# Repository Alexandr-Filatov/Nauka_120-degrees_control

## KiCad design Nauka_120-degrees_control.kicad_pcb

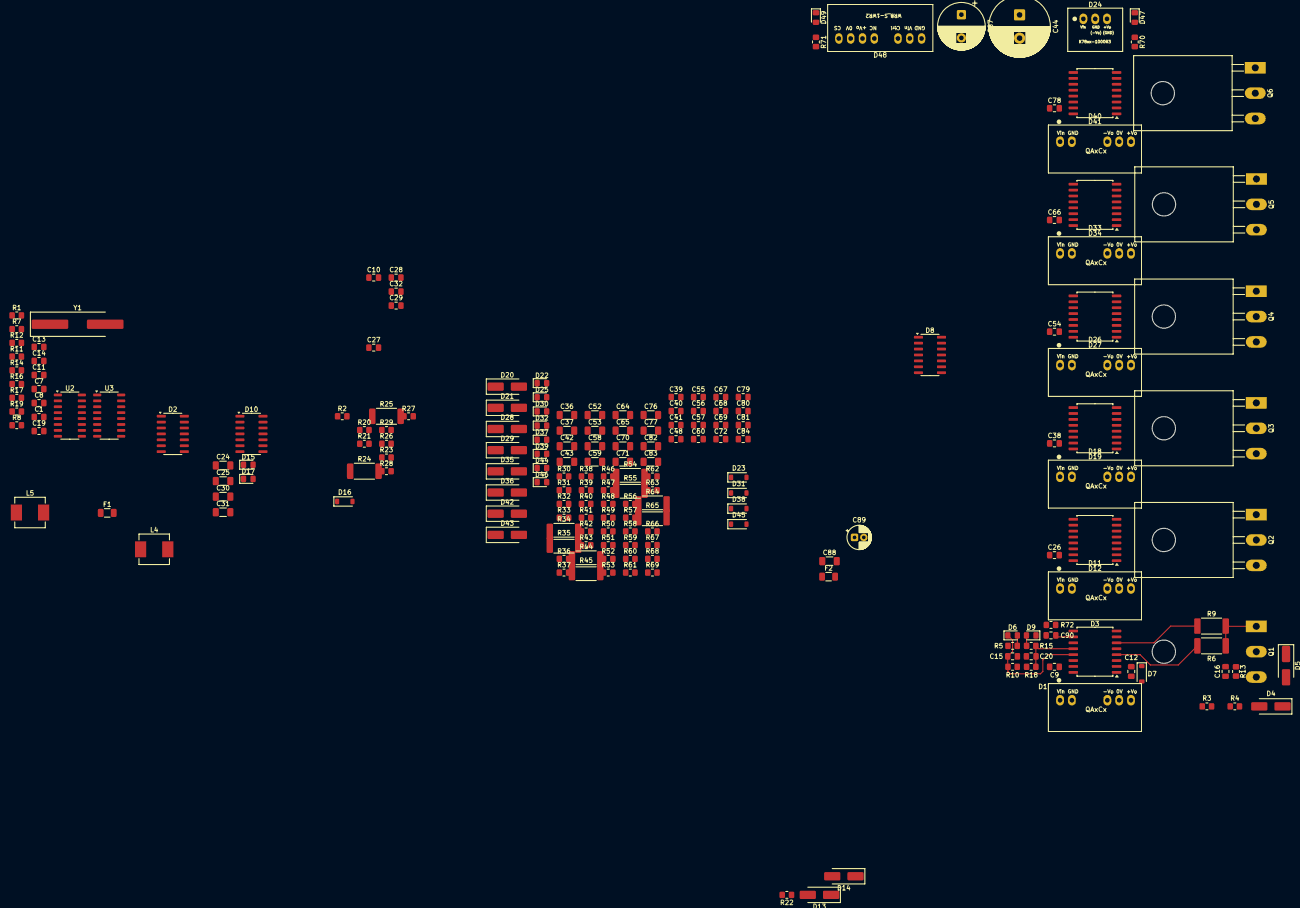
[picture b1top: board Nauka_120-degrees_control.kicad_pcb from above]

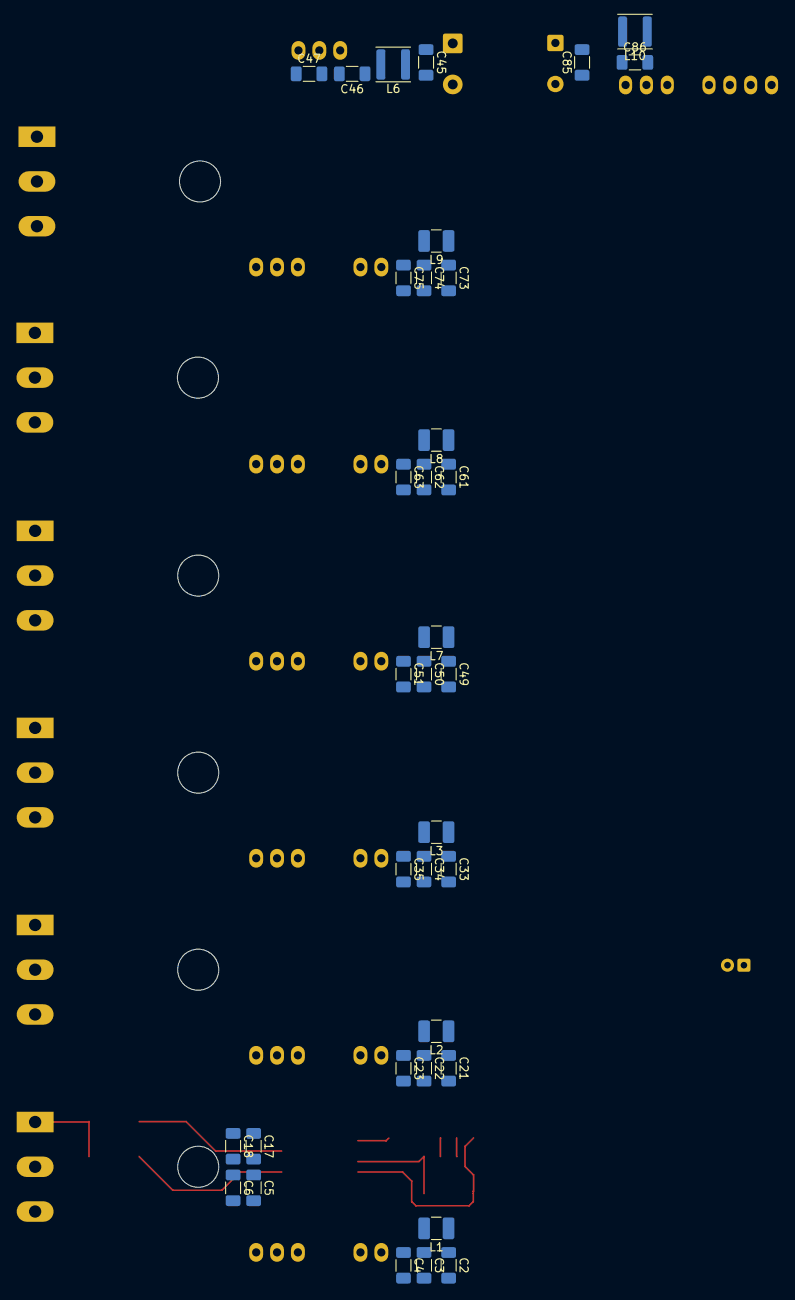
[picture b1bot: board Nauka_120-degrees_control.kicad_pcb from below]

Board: 4 copper layers, 232 parts (35 on the bottom side), 130 nets.

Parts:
C1, C7, C8, C10, C11, C19: 100n; C_0805_2012Metric_Pad1.18x1.45mm_HandSolder
C2, C3, C21, C22, C33, C34, C45, C49, C50, C61, C62, C73, C74, C85: 4.7u; C_1206_3216Metric_Pad1.33x1.80mm_HandSolder
C4, C23, C35, C51, C63, C75: 100p; C_1206_3216Metric_Pad1.33x1.80mm_HandSolder
C5, C6, C17, C18, C24, C25, C30, C31, C36, C37, C42, C43, C46, C52, C53, C58, C59, C64, C65, C70, C71, C76, C77, C82, C83, C86, C88: 10u; C_1206_3216Metric_Pad1.33x1.80mm_HandSolder
C9, C26, C38, C54, C66, C78: 2.2u; C_0805_2012Metric_Pad1.18x1.45mm_HandSolder
C12, C27, C39, C55, C67, C79: 100p; C_0805_2012Metric_Pad1.18x1.45mm_HandSolder
C13, C14: 20p; C_0805_2012Metric_Pad1.18x1.45mm_HandSolder
C15, C20, C29, C32, C40, C48, C57, C60, C68, C72, C81, C84, C90: 56p; C_0805_2012Metric_Pad1.18x1.45mm_HandSolder
C16, C28, C41, C56, C69, C80: 10n; C_0805_2012Metric_Pad1.18x1.45mm_HandSolder
C44: 680u; CP_Radial_D13.0mm_P5.00mm
C47: 22u; C_1206_3216Metric_Pad1.33x1.80mm_HandSolder
C87: 330u; CP_Radial_D10.0mm_P5.00mm
C89: 100u; CP_Radial_D5.0mm_P2.00mm
D1, D11, D18, D26, D33, D40: QA151C3; QAxCx
D2, D10: SOIC-14_3.9x8.7mm_P1.27mm
D3, D12, D19, D27, D34, D41: NSI6651; SOIC-16W_7.5x10.3mm_P1.27mm
D4, D5, D13, D14, D20, D21, D28, D29, D35, D36, D42, D43: D_Small; D_SMA_Handsoldering
D6, D9, D15, D17, D22, D25, D30, D32, D37, D39, D44, D46, D47, D49: LED_0805_2012Metric_Pad1.15x1.40mm_HandSolder
D7, D16, D23, D31, D38, D45: D_SOD-123
D8: SO-14_3.9x8.65mm_P1.27mm
D24: K7815-1000R3; K78xx-1000R3
D48: WRB2405S-1WR2; WRB_S-1WR2
F1, F2: 0466002.NR; Fuse_1206_3216Metric
L1, L2, L3, L7, L8, L9: 22u; L_1210_3225Metric_Pad1.42x2.65mm_HandSolder
L4, L5: 47u; L_Vishay_IHLP-2525
L6: 12u; L_APV_ANR4030
L10: 4.7u; L_APV_ANR4030
Q1, Q2, Q3, Q4, Q5, Q6: C2M0280120D; TO-247-3_Horizontal_TabUp
R1: 10M; R_0805_2012Metric_Pad1.20x1.40mm_HandSolder
R2, R20, R30, R40, R50, R60: 510; R_0805_2012Metric_Pad1.20x1.40mm_HandSolder
R3, R5, R18, R21, R23, R29, R31, R33, R39, R41, R43, R49, R51, R53, R59, R61, R63, R69, R71: 1k; R_0805_2012Metric_Pad1.20x1.40mm_HandSolder
R4, R22, R32, R42, R52, R62: Rdesat; R_0805_2012Metric_Pad1.20x1.40mm_HandSolder
R6, R9, R24, R25, R34, R35, R44, R45, R54, R55, R64, R65: 3; R_2512_6332Metric_Pad1.40x3.35mm_HandSolder
R7: 100k; R_0805_2012Metric_Pad1.20x1.40mm_HandSolder
R8, R11, R12, R14, R16, R17, R19: 0; R_0805_2012Metric_Pad1.20x1.40mm_HandSolder
R10, R13, R26, R27, R36, R37, R46, R47, R56, R57, R66, R67: 10k; R_0805_2012Metric_Pad1.20x1.40mm_HandSolder
R15, R28, R38, R48, R58, R68: 560; R_0805_2012Metric_Pad1.20x1.40mm_HandSolder
R70: 3k; R_0805_2012Metric_Pad1.20x1.40mm_HandSolder
R72: 120; R_0805_2012Metric_Pad1.20x1.40mm_HandSolder
U2: 4040; SO-16_3.9x9.9mm_P1.27mm
U3: 4017; SO-16_3.9x9.9mm_P1.27mm
Y1: 4.9152M; Crystal_SMD_HC49-SD_HandSoldering

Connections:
+5V: C1.2, C7.2, C8.2, C9.2, C10.2, C11.2, C19.2, C26.2, C38.2, C54.2, C66.2, C78.2, C89.1, D2.14 (VCC), D3.15 (Vcc1), D8.14 (VCC), D10.14 (VCC), D12.15 (Vcc1), D19.15 (Vcc1), D27.15 (Vcc1), D34.15 (Vcc1), D41.15 (Vcc1), D48.6 (+Vo), R5.2, R10.2, R18.2, R23.2, R26.2, R29.2, R33.2, R36.2, R39.2, R43.2, R46.2, R49.2, R53.2, R56.2, R59.2, R63.2, R66.2, R69.2, R71.2, U2.16 (VDD), U3.16 (VDD)
+15V: C2.1, C21.1, C33.1, C47.1, C49.1, C61.1, C73.1, D24.3 (+Vo(GND)), L1.1, L2.1, L3.1, L7.1, L8.1, L9.1, R70.2
+15V_H1: C5.2, C6.2, D1.7 (+Vo), D3.5 (Vcc2), R2.2
+15V_H2: C36.2, C37.2, D18.7 (+Vo), D19.5 (Vcc2), R30.2
+15V_H3: C64.2, C65.2, D33.7 (+Vo), D34.5 (Vcc2), R50.2
+15V_L1: C24.2, C25.2, D11.7 (+Vo), D12.5 (Vcc2), R20.2
+15V_L2: C52.2, C53.2, D26.7 (+Vo), D27.5 (Vcc2), R40.2
+15V_L3: C76.2, C77.2, D40.7 (+Vo), D41.5 (Vcc2), R60.2
+27V: F1.1, F2.1
-4V_H1: C17.1, C18.1, D1.5 (-Vo), D3.1 (Vee2), D3.8 (Vee2)
-4V_H2: C42.1, C43.1, D18.5 (-Vo), D19.1 (Vee2), D19.8 (Vee2)
-4V_H3: C70.1, C71.1, D33.5 (-Vo), D34.1 (Vee2), D34.8 (Vee2)
-4V_L1: C30.1, C31.1, D11.5 (-Vo), D12.1 (Vee2), D12.8 (Vee2)
-4V_L2: C58.1, C59.1, D26.5 (-Vo), D27.1 (Vee2), D27.8 (Vee2)
-4V_L3: C82.1, C83.1, D40.5 (-Vo), D41.1 (Vee2), D41.8 (Vee2)
A: C5.1, C6.1, C12.1, C16.2, C17.2, C18.2, D1.6 (0V), D3.3 (GND2), D7.2 (A), D14.1 (K), Q1.3 (S), Q2.2 (D), R13.1
B: C36.1, C37.1, C39.1, C41.2, C42.2, C43.2, D18.6 (0V), D19.3 (GND2), D23.2 (A), D29.1 (K), Q3.3 (S), Q4.2 (D), R37.1
C: C64.1, C65.1, C67.1, C69.2, C70.2, C71.2, D33.6 (0V), D34.3 (GND2), D38.2 (A), D43.1 (K), Q5.3 (S), Q6.2 (D), R57.1
G1H: C90.1, D3.10 (IN+), R72.1
G1L: D8.8 (4Y), D12.10 (IN+)
G2H: D8.4 (2Y), D19.10 (IN+)
G2L: D8.10 (5Y), D27.10 (IN+)
G3H: D8.6 (3Y), D34.10 (IN+)
G3L: D8.12 (6Y), D41.10 (IN+)
GND: C1.1, C7.1, C8.1, C9.1, C10.1, C11.1, C13.1, C14.1, C15.2, C19.1, C20.2, C26.1, C29.2, C32.2, C38.1, C40.2, C48.2, C54.1, C57.2, C60.2, C66.1, C68.2, C72.2, C78.1, C81.2, C84.2, C88.1, C89.2, C90.2, D2.5 (2C), D2.7 (GND), D2.11 (3C), D2.13 (1C), D3.9 (GND1), D3.11 (IN-), D3.16 (TEST), D8.7 (GND), D9.1 (K), D10.7 (GND), D10.11 (3C), D10.13 (1C), D12.9 (GND1), D12.11 (IN-), D12.16 (TEST), D17.1 (K), D19.9 (GND1), D19.11 (IN-), D19.16 (TEST), D25.1 (K), D27.9 (GND1), D27.11 (IN-), D27.16 (TEST), D32.1 (K), D34.9 (GND1), D34.11 (IN-), D34.16 (TEST), D39.1 (K), D41.9 (GND1), D41.11 (IN-), D41.16 (TEST), D46.1 (K), D48.7 (0V), D49.1 (K), R8.2, R12.2, U2.8 (VSS), U3.8 (VSS)
GNDPWR: C24.1, C25.1, C27.1, C28.2, C30.2, C31.2, C52.1, C53.1, C55.1, C56.2, C58.2, C59.2, C76.1, C77.1, C79.1, C80.2, C82.2, C83.2, D11.6 (0V), D12.3 (GND2), D16.2 (A), D26.6 (0V), D27.3 (GND2), D31.2 (A), D40.6 (0V), D41.3 (GND2), D45.2 (A), Q2.3 (S), Q4.3 (S), Q6.3 (S), R27.1, R47.1, R67.1
GND_IN: C2.2, C3.2, C4.2, C21.2, C22.2, C23.2, C33.2, C34.2, C35.2, C44.2, C45.2, C46.2, C47.2, C49.2, C50.2, C51.2, C61.2, C62.2, C63.2, C73.2, C74.2, C75.2, C85.1, C86.1, C87.2, D1.2 (GND), D11.2 (GND), D18.2 (GND), D24.2 (GND(-Vo)), D26.2 (GND), D33.2 (GND), D40.2 (GND), D47.1 (K), D48.1 (GND)
GateH1: C16.1, C41.1, C69.1, D3.7 (CLAMP), D19.7 (CLAMP), D34.7 (CLAMP), Q1.1 (G), Q3.1 (G), Q5.1 (G), R6.2, R9.2, R13.2, R34.2, R35.2, R37.2, R54.2, R55.2, R57.2
GateL1: C28.1, C56.1, C80.1, D12.7 (CLAMP), D27.7 (CLAMP), D41.7 (CLAMP), Q2.1 (G), Q4.1 (G), Q6.1 (G), R24.2, R25.2, R27.2, R44.2, R45.2, R47.2, R64.2, R65.2, R67.2
unnamed: C13.2, R1.1, Y1.2
unnamed: C14.2, R7.2, Y1.1
unnamed: C44.1, C45.1, L5.2, L6.1
unnamed: C85.2, C87.1, F2.2, L10.2
unnamed: C3.1, C4.1, D1.1 (Vin), L1.2
unnamed: D2.12 (1Y), D8.1 (1A)
unnamed: D2.6 (2Y), D8.3 (2A)
unnamed: D2.8 (3Y), D8.5 (3A)
unnamed: C12.2, D3.2 (DESAT), D7.1 (K), R3.1
unnamed: D3.4 (OUTH), R6.1
unnamed: D3.6 (OUTL), R9.1
unnamed: C20.1, D3.12 (RDY), R15.2, R18.1
unnamed: C15.1, D3.13 (~FLT), D6.1 (K), R10.1
unnamed: D4.2 (A), R4.1
unnamed: D4.1 (K), D5.2 (A)
unnamed: D6.2 (A), R5.1
unnamed: D8.2 (1Y), R72.2
unnamed: D9.2 (A), R15.1
unnamed: D8.9 (4A), D10.12 (1Y)
unnamed: D8.11 (5A), D10.6 (2Y)
unnamed: D8.13 (6A), D10.8 (3Y)
unnamed: C22.1, C23.1, D11.1 (Vin), L2.2
unnamed: C27.2, D12.2 (DESAT), D16.1 (K), R21.1
unnamed: D12.4 (OUTH), R24.1
unnamed: D12.6 (OUTL), R25.1
unnamed: C32.1, D12.12 (RDY), R28.2, R29.1
unnamed: C29.1, D12.13 (~FLT), D15.1 (K), R26.1
unnamed: D13.2 (A), R22.1
unnamed: D13.1 (K), D14.2 (A)
unnamed: D15.2 (A), R23.1
unnamed: D17.2 (A), R28.1
unnamed: C34.1, C35.1, D18.1 (Vin), L3.2
unnamed: C39.2, D19.2 (DESAT), D23.1 (K), R31.1
unnamed: D19.4 (OUTH), R34.1
unnamed: D19.6 (OUTL), R35.1
unnamed: C48.1, D19.12 (RDY), R38.2, R39.1
unnamed: C40.1, D19.13 (~FLT), D22.1 (K), R36.1
unnamed: D20.2 (A), R32.1
unnamed: D20.1 (K), D21.2 (A)
unnamed: D22.2 (A), R33.1
unnamed: C46.1, D24.1 (Vin), L6.2
unnamed: D25.2 (A), R38.1
unnamed: C50.1, C51.1, D26.1 (Vin), L7.2
unnamed: C55.2, D27.2 (DESAT), D31.1 (K), R41.1
unnamed: D27.4 (OUTH), R44.1
unnamed: D27.6 (OUTL), R45.1
unnamed: C60.1, D27.12 (RDY), R48.2, R49.1
unnamed: C57.1, D27.13 (~FLT), D30.1 (K), R46.1
unnamed: D28.2 (A), R42.1
unnamed: D28.1 (K), D29.2 (A)
unnamed: D30.2 (A), R43.1
unnamed: D32.2 (A), R48.1
unnamed: C62.1, C63.1, D33.1 (Vin), L8.2
unnamed: C67.2, D34.2 (DESAT), D38.1 (K), R51.1
unnamed: D34.4 (OUTH), R54.1
unnamed: D34.6 (OUTL), R55.1
unnamed: C72.1, D34.12 (RDY), R58.2, R59.1
unnamed: C68.1, D34.13 (~FLT), D37.1 (K), R56.1
unnamed: D35.2 (A), R52.1
unnamed: D35.1 (K), D36.2 (A)
unnamed: D37.2 (A), R53.1
unnamed: D39.2 (A), R58.1
unnamed: C74.1, C75.1, D40.1 (Vin), L9.2
unnamed: C79.2, D41.2 (DESAT), D45.1 (K), R61.1
unnamed: D41.4 (OUTH), R64.1
unnamed: D41.6 (OUTL), R65.1
unnamed: C84.1, D41.12 (RDY), R68.2, R69.1
unnamed: C81.1, D41.13 (~FLT), D44.1 (K), R66.1
unnamed: D42.2 (A), R62.1
unnamed: D42.1 (K), D43.2 (A)
unnamed: D44.2 (A), R63.1
unnamed: D46.2 (A), R68.1
unnamed: D47.2 (A), R70.1
unnamed: C88.2, D48.8 (CS)
unnamed: C86.2, D48.2 (Vin), L10.1
unnamed: D49.2 (A), R71.1
unnamed: F1.2, L4.1
unnamed: L4.2, L5.1
unnamed: R1.2, R7.1
unnamed: R2.1, R3.2, R4.2
unnamed: R20.1, R21.2, R22.2
unnamed: R30.1, R31.2, R32.2
unnamed: R40.1, R41.2, R42.2
unnamed: R50.1, R51.2, R52.2
unnamed: R60.1, R61.2, R62.2
unnamed: R14.1, U2.12 (Q8)
unnamed: R16.1, U2.14 (Q9)
unnamed: R17.1, U2.15 (Q10)
unnamed: R19.1, U2.1 (Q11)
unnamed: R11.1, R12.1, U2.11 (Reset)
unnamed: R8.1, U3.13 (CKEN)
unnamed: R14.2, R16.2, R17.2, R19.2, U3.14 (CLK)
Q0: D2.1 (1A), D10.3 (2A), U3.3 (Q0)
Q1: D2.2 (1B), D10.9 (3A), U3.2 (Q1)
Q2: D2.3 (2A), D10.10 (3B), U3.4 (Q2)
Q3: D2.4 (2B), D10.1 (1A), U3.7 (Q3)
Q4: D2.9 (3A), D10.2 (1B), U3.10 (Q4)
Q5: D2.10 (3B), D10.4 (2B), U3.1 (Q5)
Q6: D10.5 (2C), U3.5 (Q6), U3.15 (Reset)
RST: D3.14 (~RST), D12.14 (~RST), D19.14 (~RST), D27.14 (~RST), D34.14 (~RST), D41.14 (~RST)
VDC: D5.1 (K), D21.1 (K), D36.1 (K), Q1.2 (D), Q3.2 (D), Q5.2 (D)

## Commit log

2026-01-15 zero commit
2026-01-16 VER1.0: накидал схему управления затворами
2026-01-19 VER1.0: изменил логические И на трехвходные И-НЕ
2026-01-20 VER1.0: добавил драйвера
2026-01-21 VER1.0: начал раскидку компонентов на плате
